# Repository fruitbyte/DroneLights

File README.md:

<h1 align="center">DroneLights</h1>
<h3 align="center">A really bright light for your drone</h3>

---

Drone lights help light up your aircraft for night flying and ease of observation in the daytime. This specific drone light PCB also doubles as a simple breakout board for the ATTiny84A. This was built so that [UBC UAS](https://www.ubcuas.com/) can fly and test whenever the weather cooperates!

## Project Directory
- Manuals: PCB Assembly/Programming Info
- PCB: KiCad project files (KiCad 6.0+)
- Programming: Code for the ATTiny84A

## Features
- On/Off switch
- Breakout pins for ATtiny84A prototyping
- Labelled programming pins
- Programmable pin LED
- On indicator
- Reset and configurable pushbuttons
- Adjustable brightness and blink interval
- External input
- Zip-tie-able

## Warnings
Please build and test with caution. Do not look directly into the light at any point when testing. May cause eye damage.

## To Do
### Code
- [ ] Add different blink modes, toggled by signal pin beside power port/I2C/SPI
- [ ] Get rid of press and hold for mode switch (instead of delays in main loop, use millis function), use some form of debounce

### PCB Rev B Notes
- [ ] Add a 5V fuse to protect sensitive components
- [ ] Add diode markings to silkscreen
- [ ] Fix incorrectly labelled MOSI/MISO silkscreen on programming pins
- [ ] Use proper header spacing on breakout pins so that headers can be soldered if desired
- [ ] Remove unnecessary components for compact version (programming, breakouts, unnecessary diodes, etc.)
- [ ] Use a smaller toggle sliding switch for SW3

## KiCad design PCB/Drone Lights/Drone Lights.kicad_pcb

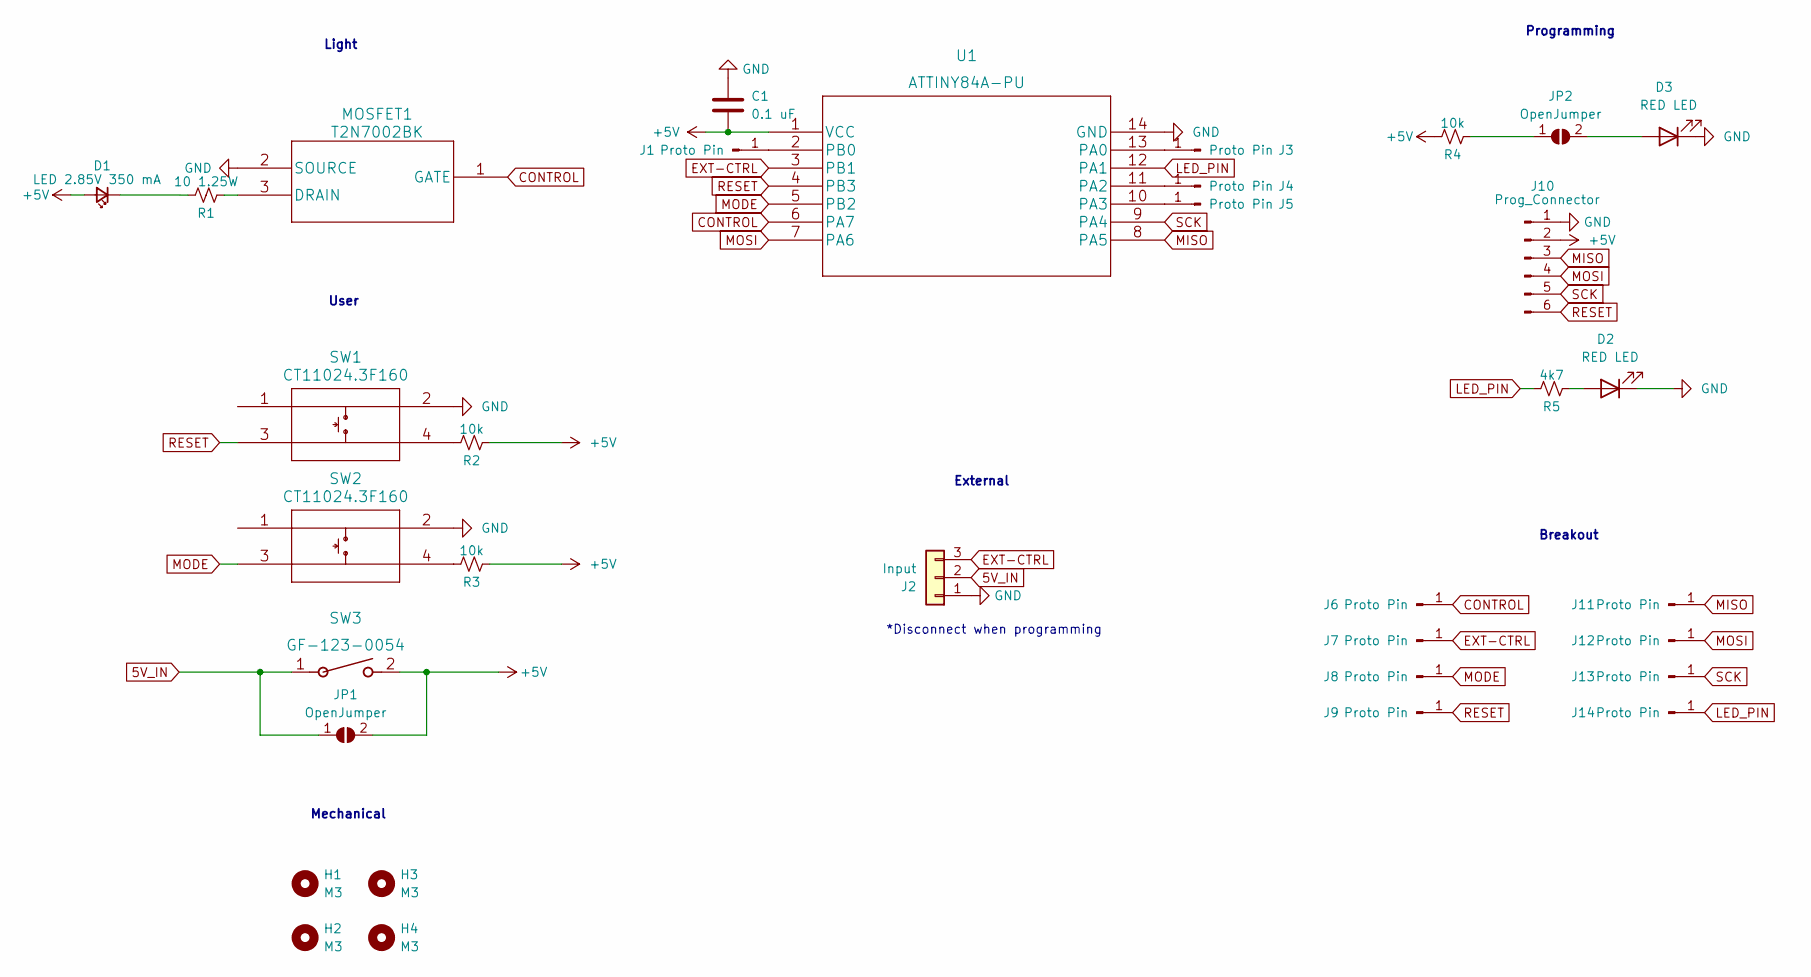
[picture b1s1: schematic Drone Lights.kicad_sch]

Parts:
C1: 0.1 uF; C_0603_1608Metric_Pad1.08x0.95mm_HandSolder; MPN C1608X7R1H104K080AA; Digikey No. 445-1314-1-ND
D1: LED 2.85V 350 mA; XLAMP_LED_XPE2
D2, D3: RED LED; R_0603_1608Metric_Pad0.98x0.95mm_HandSolder; MPN B1911USD-20D000114U1930; Digikey No. 3147-B1911USD-20D000114U1930CT-ND
H1, H2, H3, H4: M3; MountingHole_3.2mm_M3
J1, J3, J4, J5, J6, J7, J8, J9, J11, J12, J13, J14: Proto Pin; Pin_D1.0mm_L10.0mm
J2: Input; PinHeader_1x03_P2.54mm_Vertical
J10: Prog_Connector; PinHeader_1x06_P2.54mm_Vertical
JP1, JP2: OpenJumper; SolderJumper-2_P1.3mm_Open_RoundedPad1.0x1.5mm
MOSFET1: T2N7002BK; MPN T2N7002BK,LM; Digikey No. T2N7002BKLMCT-ND
R1: 10 1.25W; R_0603_1608Metric_Pad0.98x0.95mm_HandSolder; MPN CRGP2010F10R; Digikey No. A130636CT-ND
R2, R3, R4: 10k; R_0603_1608Metric_Pad0.98x0.95mm_HandSolder; MPN RNCP0603FTD10K0; Digikey No. RNCP0603FTD10K0CT-ND
R5: 4k7; R_0603_1608Metric_Pad0.98x0.95mm_HandSolder; MPN RK73H1JRTTD4701F; Digikey No. 2019-RK73H1JRTTD4701FCT-ND
SW1, SW2: CT11024.3F160; MPN CT11024.3F160; Digikey No. 2449-CT11024.3F160-ND
SW3: GF-123-0054; MPN GF-123-0054; Digikey No. CWI333-ND
U1: ATTINY84A-PU; MPN ATTINY84A-PU; Digikey No. ATTINY84A-PU-ND

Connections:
5V_IN: J2.2, JP1.1 (A), SW3.1
+5V: C1.1, D1.2 (A), J10.2, JP1.2 (B), R2.2, R3.2, R4.1, SW3.2, U1.1 (VCC)
CONTROL: J6.1, MOSFET1.1 (GATE), U1.6 (PA7)
EXT-CTRL: J2.3, J7.1, U1.3 (PB1)
GND: C1.2, D2.1 (K), D3.1 (K), J2.1, J10.1, MOSFET1.2 (SOURCE), SW1.2, SW2.2, U1.14 (GND)
LED_PIN: J14.1, R5.1, U1.12 (PA1)
MISO: J10.3, J11.1, U1.8 (PA5)
MODE: J8.1, SW2.3, U1.5 (PB2)
MOSI: J10.4, J12.1, U1.7 (PA6)
unnamed: D1.1 (K), R1.1
unnamed: D2.2 (A), R5.2
unnamed: D3.2 (A), JP2.2 (B)
unnamed: J1.1, U1.2 (PB0)
unnamed: J3.1, U1.13 (PA0)
unnamed: J4.1, U1.11 (PA2)
unnamed: J5.1, U1.10 (PA3)
unnamed: JP2.1 (A), R4.2
unnamed: MOSFET1.3 (DRAIN), R1.2
unnamed: R2.1, SW1.4
unnamed: R3.1, SW2.4
RESET: J9.1, J10.6, SW1.3, U1.4 (PB3)
SCK: J10.5, J13.1, U1.9 (PA4)

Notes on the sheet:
Programming
User
External
Light
*Disconnect when programming
Mechanical
Breakout

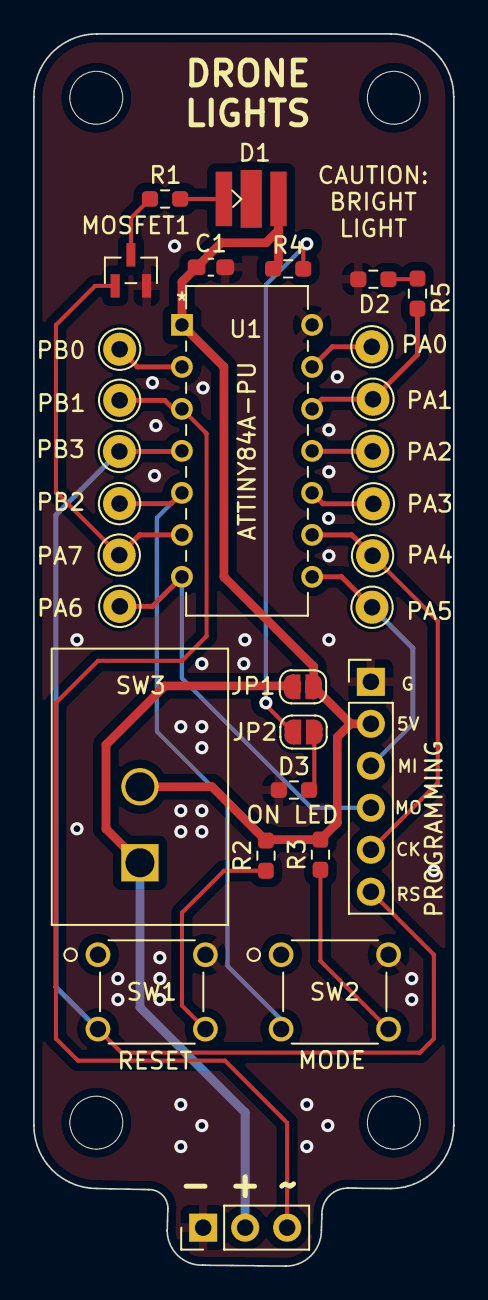
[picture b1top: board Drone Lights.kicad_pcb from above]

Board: 2 copper layers, 25.4 x 74.5 mm, 34 parts (0 on the bottom side), 22 nets.

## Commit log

2022-09-29 Init structure
2022-09-29 Fix readme
2022-09-29 Added safety and code comments
2022-09-29 Updated assembly guide
2022-09-29 Assemblyguide updates
2022-10-24 Updated with local copy

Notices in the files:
parts and their libraries:
Copyright 2021 Accelerated Designs. All rights reserved.
